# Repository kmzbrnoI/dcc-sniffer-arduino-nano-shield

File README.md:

Arduino Nano DCC Sniffer shield
===============================

This repository contains:

1. schematic & PCB layout for Arduino Nano DCC Sniffer,
2. firmware for Arduino Nano to read packets,
3. software in python to read serial stream from Arduino Nano and store
   stream content in file.

Arduino Nano firmware is based on
[rudysmodelrailway project](https://rudysmodelrailway.wordpress.com/2015/10/23/dcc-sniffer-packet-analyser-with-arduino/).

Created by Jan Malina.

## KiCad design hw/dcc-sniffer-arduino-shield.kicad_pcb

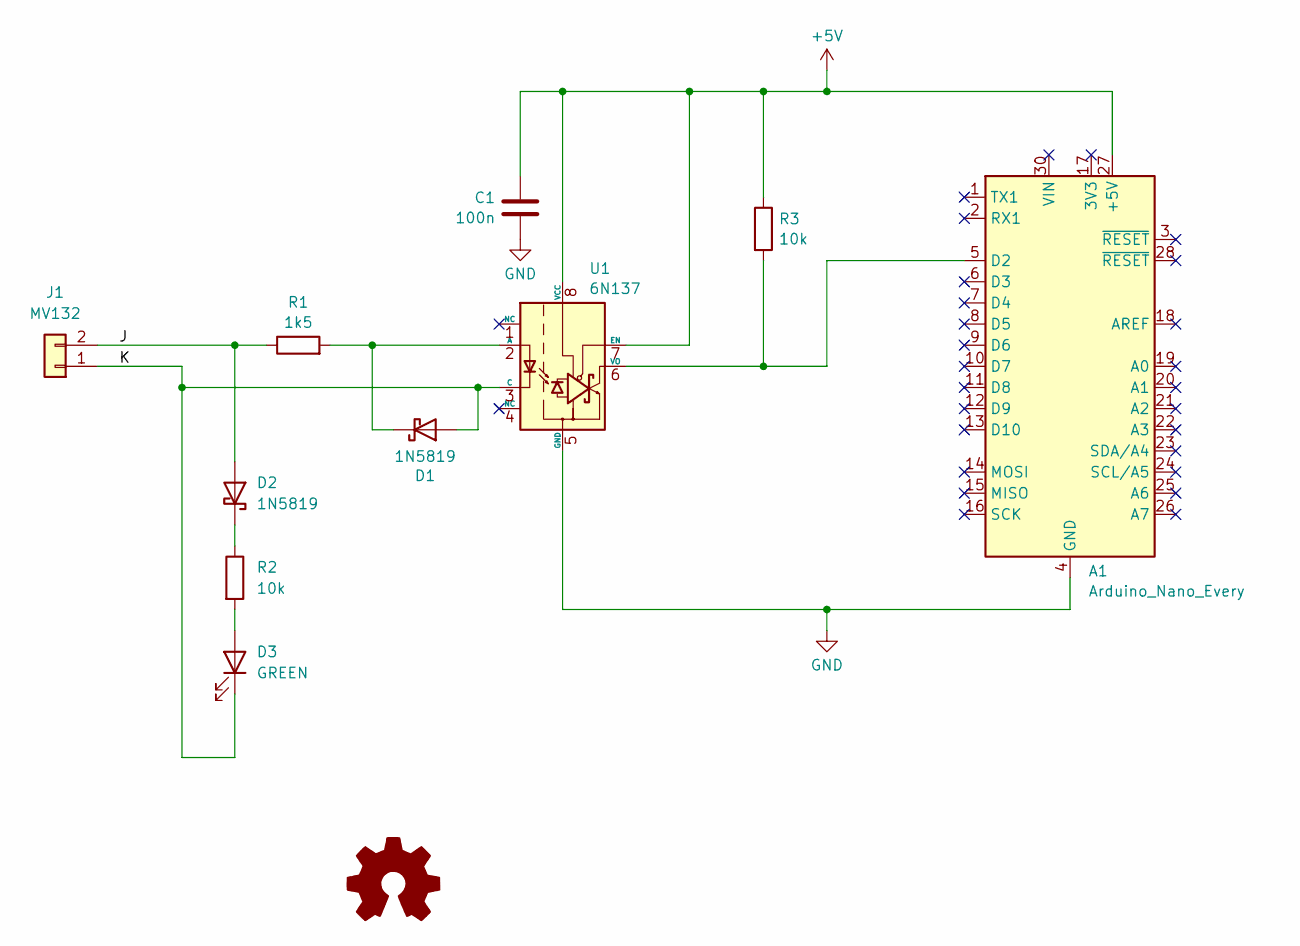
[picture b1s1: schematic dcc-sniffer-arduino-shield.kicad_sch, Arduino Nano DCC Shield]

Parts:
A1: Arduino_Nano_Every; Arduino_Nano
C1: 100n; C_0805_2012Metric_Pad1.18x1.45mm_HandSolder
D1, D2: 1N5819; D_SOD-123; LCSC C8598
D3: GREEN; LED_0805_2012Metric_Pad1.15x1.40mm_HandSolder
J1: MV132; TerminalBlock_4Ucon_1x02_P3.50mm_Horizontal
R1: 1k5; R_0805_2012Metric_Pad1.20x1.40mm_HandSolder
R2, R3: 10k; R_0805_2012Metric_Pad1.20x1.40mm_HandSolder
U1: 6N137; DIP-8_W7.62mm_LongPads

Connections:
+5V: A1.27 (+5V), C1.1, R3.1, U1.7 (EN), U1.8 (VCC)
/J: D2.2 (A), J1.2, R1.1
/K: D1.2 (A), D3.1 (K), J1.1, U1.3 (C)
GND: A1.4 (GND), A1.29 (GND), C1.2, U1.5 (GND)
unnamed: A1.5 (D2), R3.2, U1.6 (VO)
unnamed: D1.1 (K), R1.2, U1.2 (A)
unnamed: D2.1 (K), R2.1
unnamed: D3.2 (A), R2.2

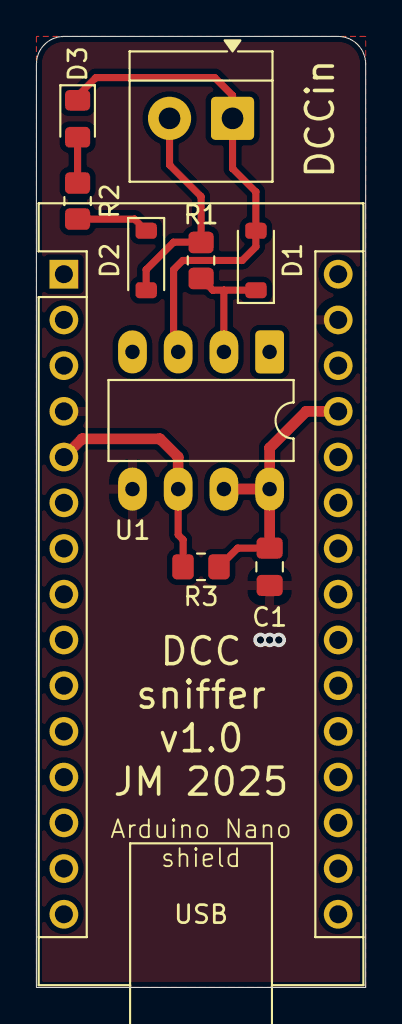
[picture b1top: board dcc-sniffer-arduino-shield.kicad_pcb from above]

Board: 2 copper layers, 18.3 x 52.8 mm, 10 parts (0 on the bottom side), 8 nets.

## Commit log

2026-01-04 Add KiCad project & schematic.
2026-01-04 Add README & .gitignore.
2026-01-04 Mark DCC input pin D2.
2026-01-04 Route PCB.
2026-01-04 Add penguin graphic.
2026-01-04 Move PCB to 'hw' folder.
2026-01-04 Add RB_DCC_Sniffer_v2.ino.
2026-01-04 Fix address decoding.
2026-01-04 Remove spaces at EOL.
2026-01-04 Tweak default values.
2026-01-04 Print 'unknown instruction type'.
2026-01-04 Formality: fix indentation.
2026-01-04 Remove non-existing options.
2026-01-04 Print packet when it arrives.
2026-01-04 Tweak defailt params: refresh time = 1 s, USB baudrate = 115200.
2026-01-04 Add more information to README.
2026-01-04 Do not print millis.
2026-01-04 Add sniffer_logger.py script.

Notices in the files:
dcc-sniffer-arduino-shield.kicad_sch:
https://creativecommons.org/licenses/by-sa/4.0
Released under the Creative Commons Attribution-ShareAlike 4.0 License
